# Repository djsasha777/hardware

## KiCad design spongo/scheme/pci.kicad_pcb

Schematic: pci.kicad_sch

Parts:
C1, C2, C3, C4, C5, C6, C7, C8, C9, C10, C11, C12, C13, C14, C15, C16, C17, C18, C19, C20: 0.1uF; D_0603_1608Metric
C2KV1, C2KV2, C2KV3, C2KV4, C2KV5: LD125C274JAB2A; CAPC4532X127N
C200: SIM; D_0603_1608Metric
CSIM1, CSIM2, CSIM3, CSIM4: 33pF; D_0603_1608Metric
IC1, IC2, IC3, IC4, IC5: TMC429-PI24; my-sop-24
J1: Bus_PCI_Express_Mini; BUS_PCI_Express_Mini_Half
J3, J6: Conn_02x09_Odd_Even; PinSocket_2x09_P2.54mm_Vertical
J4: USB4056-03-A_REVA; GCT_USB4056-03-A_REVA; PARTREV A
J5: HDMI_A; HDMI_A_Molex_208658-1001_Horizontal
J7: 1932258-1; CONN_1932258-1
J8: DM3BT-DSF-PEJS; HRS_DM3BT-DSF-PEJS; PARTREV N/A
J9: 78727-0001; 78727-0001_1; Mouser_Part_Number 538-78727-0001
J10: Bus_M.2_Socket_B; TE_1-2199119-0
J11: Conn_02x01_Row_Letter_First; PinSocket_1x02_P2.54mm_Vertical
K1: G6K-2F; RELAY_G6K-2F
PS1: IRM-20-3; Converter_ACDC_MeanWell_IRM-20-xx_THT
PS2: IRM-20-5; Converter_ACDC_MeanWell_IRM-20-xx_THT
R1, R2, R3, R4, R5, R6, R7, R8, R9, R10, R11, R12, R13, R14, R15, R16, R17, R18, R19, R20: 75R; D_0603_1608Metric
RSWITCH1: 330R; D_0603_1608Metric
U1: AC-A; ac-connector
U19: CM4102008; MODULE_CM4102008; PARTREV 2021-10-12
X1, X2, X3: GLX-S-88M
conf5, conf6, conf7, conf8: 330R; D_0603_1608Metric
hlk-1: HLK-7621

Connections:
+3V3: J1.2 (+3V3AUX), J1.52 (+3V3AUX), J6.2, hlk-1.1, hlk-1.2, hlk-1.3, hlk-1.4
+5V: J3.2, J4.A4 (VBUS_A), J4.A9 (VBUS_A), J4.B4 (VBUS_B), J4.B9 (VBUS_B), J5.18 (+5V), J6.8, J7.1 (VBUS), U19.77 (+5V(INPUT)), U19.79 (+5V(INPUT)), U19.81 (+5V(INPUT)), U19.83 (+5V(INPUT)), U19.85 (+5V(INPUT)), U19.87 (+5V(INPUT))
GND: C1.1 (K), C2.1 (K), C2KV1.1, C2KV2.1, C2KV3.1, C2KV4.1, C2KV5.1, C3.1 (K), C4.1 (K), C5.1 (K), C6.1 (K), C7.1 (K), C8.1 (K), C9.1 (K), C10.1 (K), C11.1 (K), C12.1 (K), C13.1 (K), C14.1 (K), C15.1 (K), C16.1 (K), C17.1 (K), C18.1 (K), C19.1 (K), C20.1 (K), C200.1 (K), CSIM1.1 (K), CSIM2.1 (K), CSIM3.1 (K), CSIM4.1 (K), J1.4 (GND), J1.9 (GND), J1.15 (GND), J1.18 (GND), J1.21 (GND), J1.26 (GND), J1.27 (GND), J1.29 (GND), J1.34 (GND), J1.35 (GND), J1.37 (GND), J1.40 (GND), J1.43 (GND), J1.50 (GND), J1.MP, J4.A1 (GND_A), J4.A12 (GND_A), J4.B1 (GND_B), J4.B12 (GND_B), J4.S1 (SHELL_GND), J4.S2 (SHELL_GND), J4.S3 (SHELL_GND), J4.S4 (SHELL_GND), J5.2 (D2S), J5.5 (D1S), J5.8 (D0S), J5.11 (CKS), J5.17 (GND), J5.SH, J6.3, J6.7, J6.11, J6.17, J6.18, J7.4 (GND), J7.7 (GND_DRAIN), J7.S1 (SHIELD), J7.S2 (SHIELD), J8.6 (VSS), J8.S1 (SHIELD), J8.S2 (SHIELD), J8.S3 (SHIELD), J8.S4 (SHIELD), J9.5 (C5), J9.9 (GND1), J9.10 (GND2), J9.11 (GND3), J9.12 (GND4), J9.13 (GND5), J9.14 (GND6), J10.3 (GND), J10.5 (GND), J10.11 (GND), J10.27 (GND), J10.33 (GND), J10.39 (GND), J10.45 (GND), J10.51 (GND), J10.57 (GND), J10.71 (GND), J10.73 (GND), J11.a1, K1.8, PS1.3 (-Vo), PS2.3 (-Vo), RSWITCH1.2 (A), U19.1 (GND), U19.2 (GND), U19.7 (GND), U19.8 (GND), U19.13 (GND), U19.14 (GND), U19.22 (GND), U19.23 (GND), U19.32 (GND), U19.33 (GND), U19.42 (GND), U19.43 (GND), U19.52 (GND), U19.53 (GND), U19.59 (GND), U19.60 (GND), U19.65 (GND), U19.66 (GND), U19.71 (GND), U19.74 (GND), U19.98 (GND), U19.107 (GND), U19.108 (GND), U19.113 (GND), U19.114 (GND), U19.119 (GND), U19.120 (GND), U19.125 (GND), U19.126 (GND), U19.131 (GND), U19.132 (GND), U19.137 (GND), U19.138 (GND), U19.144 (GND), U19.150 (GND), U19.155 (GND), U19.156 (GND), U19.161 (GND), U19.162 (GND), U19.167 (GND), U19.168 (GND), U19.173 (GND), U19.174 (GND), U19.179 (GND), U19.180 (GND), U19.185 (GND), U19.186 (GND), U19.191 (GND), U19.192 (GND), U19.197 (GND), U19.198 (GND), hlk-1.5, hlk-1.6, hlk-1.7, hlk-1.8
unnamed: C1.2 (A), IC1.4 (REF3)
unnamed: C2.2 (A), IC1.10 (SCK_C)
unnamed: C2KV1.2, R1.2 (A), R2.2 (A), R3.2 (A), R4.2 (A)
unnamed: C2KV2.2, R5.2 (A), R6.2 (A), R7.2 (A), R8.2 (A)
unnamed: C2KV3.2, R9.2 (A), R10.2 (A), R11.2 (A), R12.2 (A)
unnamed: C2KV4.2, R13.2 (A), R14.2 (A), R15.2 (A), R16.2 (A)
unnamed: C2KV5.2, R17.2 (A), R18.2 (A), R19.2 (A), R20.2 (A)
unnamed: C3.2 (A), IC1.1 (POSCMP)
unnamed: C4.2 (A), IC1.7 (CLK)
unnamed: C5.2 (A), IC2.4 (REF3)
unnamed: C6.2 (A), IC2.10 (SCK_C)
unnamed: C7.2 (A), IC2.1 (POSCMP)
unnamed: C8.2 (A), IC2.7 (CLK)
unnamed: C9.2 (A), IC3.4 (REF3)
unnamed: C10.2 (A), IC3.10 (SCK_C)
unnamed: C11.2 (A), IC3.1 (POSCMP)
unnamed: C12.2 (A), IC3.7 (CLK)
unnamed: C13.2 (A), IC4.4 (REF3)
unnamed: C14.2 (A), IC4.10 (SCK_C)
unnamed: C15.2 (A), IC4.1 (POSCMP)
unnamed: C16.2 (A), IC4.7 (CLK)
unnamed: C17.2 (A), IC5.4 (REF3)
unnamed: C18.2 (A), IC5.10 (SCK_C)
unnamed: C19.2 (A), IC5.1 (POSCMP)
unnamed: C20.2 (A), IC5.7 (CLK)
unnamed: C200.2 (A), J8.4 (VDD), J10.2 (3.3V), J10.4 (3.3V), J10.70 (3.3V), J10.72 (3.3V), J10.74 (3.3V), U19.75 (SD_PWR_ON), U19.78 (GPIO_VREF), U19.84 (CM4_3.3V(OUTPUT)), U19.86 (CM4_3.3V(OUTPUT)), conf5.2 (A), conf6.2 (A), conf7.2 (A), conf8.2 (A)
unnamed: CSIM1.2 (A), J9.1 (C1), J10.36 (UIM-PWR)
unnamed: CSIM2.2 (A), J9.3 (C3), J10.32 (UIM-CLK)
unnamed: CSIM3.2 (A), J9.7 (C7), J10.34 (UIM-DATA)
unnamed: CSIM4.2 (A), J9.2 (C2), J10.30 (UIM-RESET)
unnamed: IC1.2 (REF1), hlk-1.63
unnamed: IC1.3 (REF2), hlk-1.64
unnamed: IC1.5 (V5@1), hlk-1.65
unnamed: IC1.6 (TEST), hlk-1.66
unnamed: IC1.8 (GND@1), hlk-1.67
unnamed: IC1.9 (~SCS_C), hlk-1.68
unnamed: IC1.11 (SDI_C), hlk-1.69
unnamed: IC1.12 (SDOZ_C), hlk-1.70
unnamed: IC1.13 (REFR2), X1.8
unnamed: IC1.14 (~INT_SDO_C), X1.7
unnamed: IC1.15 (SDO_S_S1), R1.1 (K)
unnamed: IC1.16 (SCK_S_D1), X1.5
unnamed: IC1.17 (~SCS_S_S2), X1.4
unnamed: IC1.18 (~SCS2_S3), R2.1 (K)
unnamed: IC1.19 (~SCS3_D3), X1.6
unnamed: IC1.20 (V5@2), X1.3
unnamed: IC1.21 (V33), R3.1 (K)
unnamed: IC1.22 (GND@2), X1.2
unnamed: IC1.23 (SDI_S_D2), X1.1
unnamed: IC1.24 (REFR1), R4.1 (K)
unnamed: IC2.2 (REF1), hlk-1.36
unnamed: IC2.3 (REF2), hlk-1.37
unnamed: IC2.5 (V5@1), hlk-1.38
unnamed: IC2.6 (TEST), hlk-1.39
unnamed: IC2.8 (GND@1), hlk-1.40
unnamed: IC2.9 (~SCS_C), hlk-1.41
unnamed: IC2.11 (SDI_C), hlk-1.42
unnamed: IC2.12 (SDOZ_C), hlk-1.43
unnamed: IC2.13 (REFR2), X2.8
unnamed: IC2.14 (~INT_SDO_C), X2.7
unnamed: IC2.15 (SDO_S_S1), R6.1 (K)
unnamed: IC2.16 (SCK_S_D1), X2.5
unnamed: IC2.17 (~SCS_S_S2), X2.4
unnamed: IC2.18 (~SCS2_S3), R5.1 (K)
unnamed: IC2.19 (~SCS3_D3), X2.6
unnamed: IC2.20 (V5@2), X2.3
unnamed: IC2.21 (V33), R8.1 (K)
unnamed: IC2.22 (GND@2), X2.2
unnamed: IC2.23 (SDI_S_D2), X2.1
unnamed: IC2.24 (REFR1), R7.1 (K)
unnamed: IC3.2 (REF1), hlk-1.28
unnamed: IC3.3 (REF2), hlk-1.29
unnamed: IC3.5 (V5@1), hlk-1.30
unnamed: IC3.6 (TEST), hlk-1.31
unnamed: IC3.8 (GND@1), hlk-1.32
unnamed: IC3.9 (~SCS_C), hlk-1.33
unnamed: IC3.11 (SDI_C), hlk-1.34
unnamed: IC3.12 (SDOZ_C), hlk-1.35
unnamed: IC3.13 (REFR2), X3.8
unnamed: IC3.14 (~INT_SDO_C), X3.7
unnamed: IC3.15 (SDO_S_S1), R10.1 (K)
unnamed: IC3.16 (SCK_S_D1), X3.5
unnamed: IC3.17 (~SCS_S_S2), X3.4
unnamed: IC3.18 (~SCS2_S3), R9.1 (K)
unnamed: IC3.19 (~SCS3_D3), X3.6
unnamed: IC3.20 (V5@2), X3.3
unnamed: IC3.21 (V33), R12.1 (K)
unnamed: IC3.22 (GND@2), X3.2
unnamed: IC3.23 (SDI_S_D2), X3.1
unnamed: IC3.24 (REFR1), R11.1 (K)
unnamed: IC4.2 (REF1), hlk-1.45
unnamed: IC4.3 (REF2), hlk-1.46
unnamed: IC4.5 (V5@1), hlk-1.47
unnamed: IC4.6 (TEST), hlk-1.48
unnamed: IC4.8 (GND@1), hlk-1.49
unnamed: IC4.9 (~SCS_C), hlk-1.50
unnamed: IC4.11 (SDI_C), hlk-1.51
unnamed: IC4.12 (SDOZ_C), hlk-1.52
unnamed: IC4.13 (REFR2), J3.17
unnamed: IC4.14 (~INT_SDO_C), J3.15
unnamed: IC4.15 (SDO_S_S1), R14.1 (K)
unnamed: IC4.16 (SCK_S_D1), J3.11
unnamed: IC4.17 (~SCS_S_S2), J3.9
unnamed: IC4.18 (~SCS2_S3), R13.1 (K)
unnamed: IC4.19 (~SCS3_D3), J3.13
unnamed: IC4.20 (V5@2), J3.7
unnamed: IC4.21 (V33), R15.1 (K)
unnamed: IC4.22 (GND@2), J3.5
unnamed: IC4.23 (SDI_S_D2), J3.3
unnamed: IC4.24 (REFR1), R16.1 (K)
unnamed: IC5.2 (REF1), U19.12 (ETHERNET_PAIR0_P)
unnamed: IC5.3 (REF2), U19.10 (ETHERNET_PAIR0_N)
unnamed: IC5.5 (V5@1), U19.4 (ETHERNET_PAIR1_P)
unnamed: IC5.6 (TEST), U19.6 (ETHERNET_PAIR1_N)
unnamed: IC5.8 (GND@1), U19.11 (ETHERNET_PAIR2_P)
unnamed: IC5.9 (~SCS_C), U19.9 (ETHERNET_PAIR2_N)
unnamed: IC5.11 (SDI_C), U19.3 (ETHERNET_PAIR3_P)
unnamed: IC5.12 (SDOZ_C), U19.5 (ETHERNET_PAIR3_N)
unnamed: IC5.13 (REFR2), J3.18
unnamed: IC5.14 (~INT_SDO_C), J3.16
unnamed: IC5.15 (SDO_S_S1), R18.1 (K)
unnamed: IC5.16 (SCK_S_D1), J3.12
unnamed: IC5.17 (~SCS_S_S2), J3.10
unnamed: IC5.18 (~SCS2_S3), R17.1 (K)
unnamed: IC5.19 (~SCS3_D3), J3.14
unnamed: IC5.20 (V5@2), J3.8
unnamed: IC5.21 (V33), R19.1 (K)
unnamed: IC5.22 (GND@2), J3.6
unnamed: IC5.23 (SDI_S_D2), J3.4
unnamed: IC5.24 (REFR1), R20.1 (K)
unnamed: J1.11 (REFCLK-), hlk-1.110
unnamed: J1.13 (REFCLK+), hlk-1.111
unnamed: J1.22 (~PERST), hlk-1.105
unnamed: J1.23 (PERn0), hlk-1.109
unnamed: J1.25 (PERp0), hlk-1.108
unnamed: J1.31 (PETn0), hlk-1.107
unnamed: J1.33 (PETp0), hlk-1.106
unnamed: J3.1, PS2.4 (+Vo)
unnamed: J4.A6 (DP1), J4.B6 (DP2), U19.105 (USB_P)
unnamed: J4.A7 (DN1), J4.B7 (DN2), U19.103 (USB_N)
unnamed: J5.1 (D2+), U19.170 (HDMI0_TX2_P)
unnamed: J5.3 (D2-), U19.172 (HDMI0_TX2_N)
unnamed: J5.4 (D1+), U19.176 (HDMI0_TX1_P)
unnamed: J5.6 (D1-), U19.178 (HDMI0_TX1_N)
unnamed: J5.7 (D0+), U19.182 (HDMI0_TX0_P)
unnamed: J5.9 (D0-), U19.184 (HDMI0_TX0_N)
unnamed: J5.10 (CK+), U19.188 (HDMI0_CLK_P)
unnamed: J5.12 (CK-), U19.190 (HDMI0_CLK_N)
unnamed: J5.13 (CEC), U19.151 (HDMI0_CEC)
unnamed: J5.15 (SCL), U19.200 (HDMI0_SCL)
unnamed: J5.16 (SDA), U19.199 (HDMI0_SDA)
unnamed: J5.19 (HPD), U19.153 (HDMI0_HOTPLUG)
unnamed: J6.1, PS1.4 (+Vo)
unnamed: J6.4, U19.93 (~RPIBOOT)
unnamed: J6.5, K1.3, K1.6
unnamed: J6.6, K1.4, K1.5
unnamed: J6.9, U19.28 (GPIO13)
unnamed: J6.10, U19.31 (GPIO12)
unnamed: J6.12, U19.111 (VDAC_COMP)
unnamed: J6.13, hlk-1.94
unnamed: J6.14, U19.55 (GPIO14)
unnamed: J6.15, hlk-1.93
unnamed: J6.16, U19.51 (GPIO15)
unnamed: J7.2 (D-), hlk-1.26
unnamed: J7.3 (D+), hlk-1.25
unnamed: J7.5 (STDA_SSRX-), hlk-1.23
unnamed: J7.6 (STDA_SSRX+), hlk-1.22
unnamed: J7.8 (STDA_SSTX-), hlk-1.21
unnamed: J7.9 (STDA_SSTX+), hlk-1.20
unnamed: J8.1 (DAT2), U19.69 (SD_DAT2)
unnamed: J8.2 (DAT3/CD), U19.61 (SD_DAT3)
unnamed: J8.3 (CMD), U19.62 (SD_CMD)
unnamed: J8.5 (CLK), U19.57 (SD_CLK)
unnamed: J8.7 (DAT0), U19.63 (SD_DAT0)
unnamed: J8.8 (DAT1), U19.67 (SD_DAT1)
unnamed: J10.1 (CONFIG_3), conf8.1 (K)
unnamed: J10.21 (CONFIG_0), conf5.1 (K)
unnamed: J10.41 (PERn0/SATA-B+), U19.118 (PCIE_RX_N)
unnamed: J10.43 (PERp0/SATA-B-), U19.116 (PCIE_RX_P)
unnamed: J10.47 (PETn0/SATA-A-), U19.124 (PCIE_TX_N)
unnamed: J10.49 (PETp0/SATA-A+), U19.122 (PCIE_TX_P)
unnamed: J10.50 (~PERST), U19.109 (PCIE_~RST)
unnamed: J10.52 (~CLKREQ), U19.102 (PCIE_CLK_~REQ)
unnamed: J10.53 (REFCLKn), U19.112 (PCIE_CLK_N)
unnamed: J10.55 (REFCLKp), U19.110 (PCIE_CLK_P)
unnamed: J9.8 (C8), J10.66 (SIM_DETECT)
unnamed: J10.69 (CONFIG_1), conf6.1 (K)
unnamed: J10.75 (CONFIG_2), conf7.1 (K)
unnamed: J11.b1, U19.101 (USB_OTG_ID)
unnamed: K1.1, RSWITCH1.1 (K), hlk-1.104
unnamed: PS1.1 (AC/L), PS2.1 (AC/L), U1.P$1
unnamed: PS1.2 (AC/N), PS2.2 (AC/N), U1.P$2

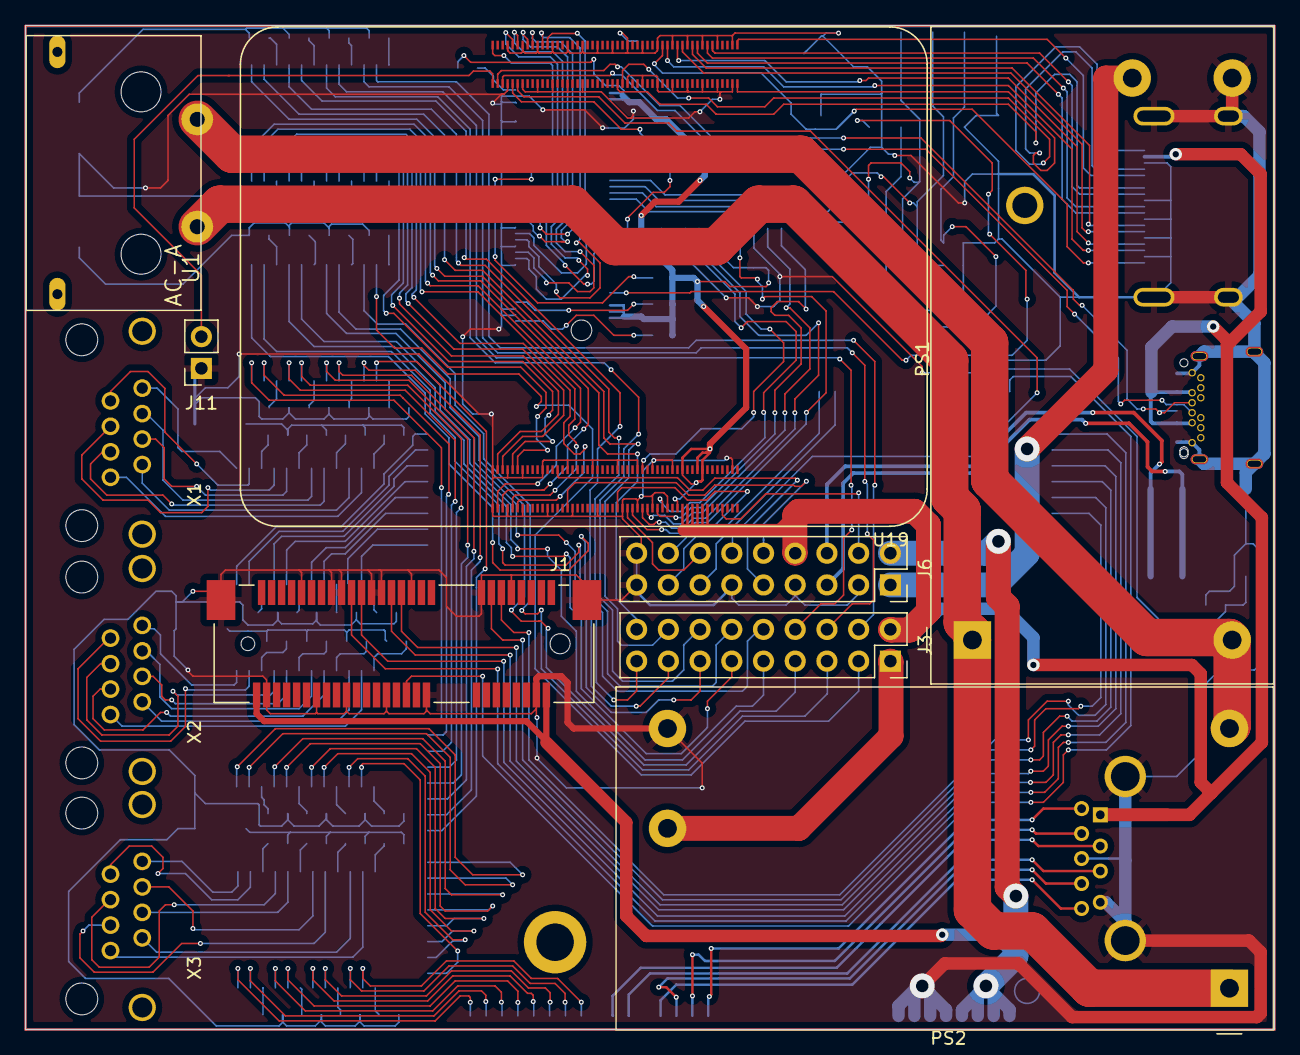
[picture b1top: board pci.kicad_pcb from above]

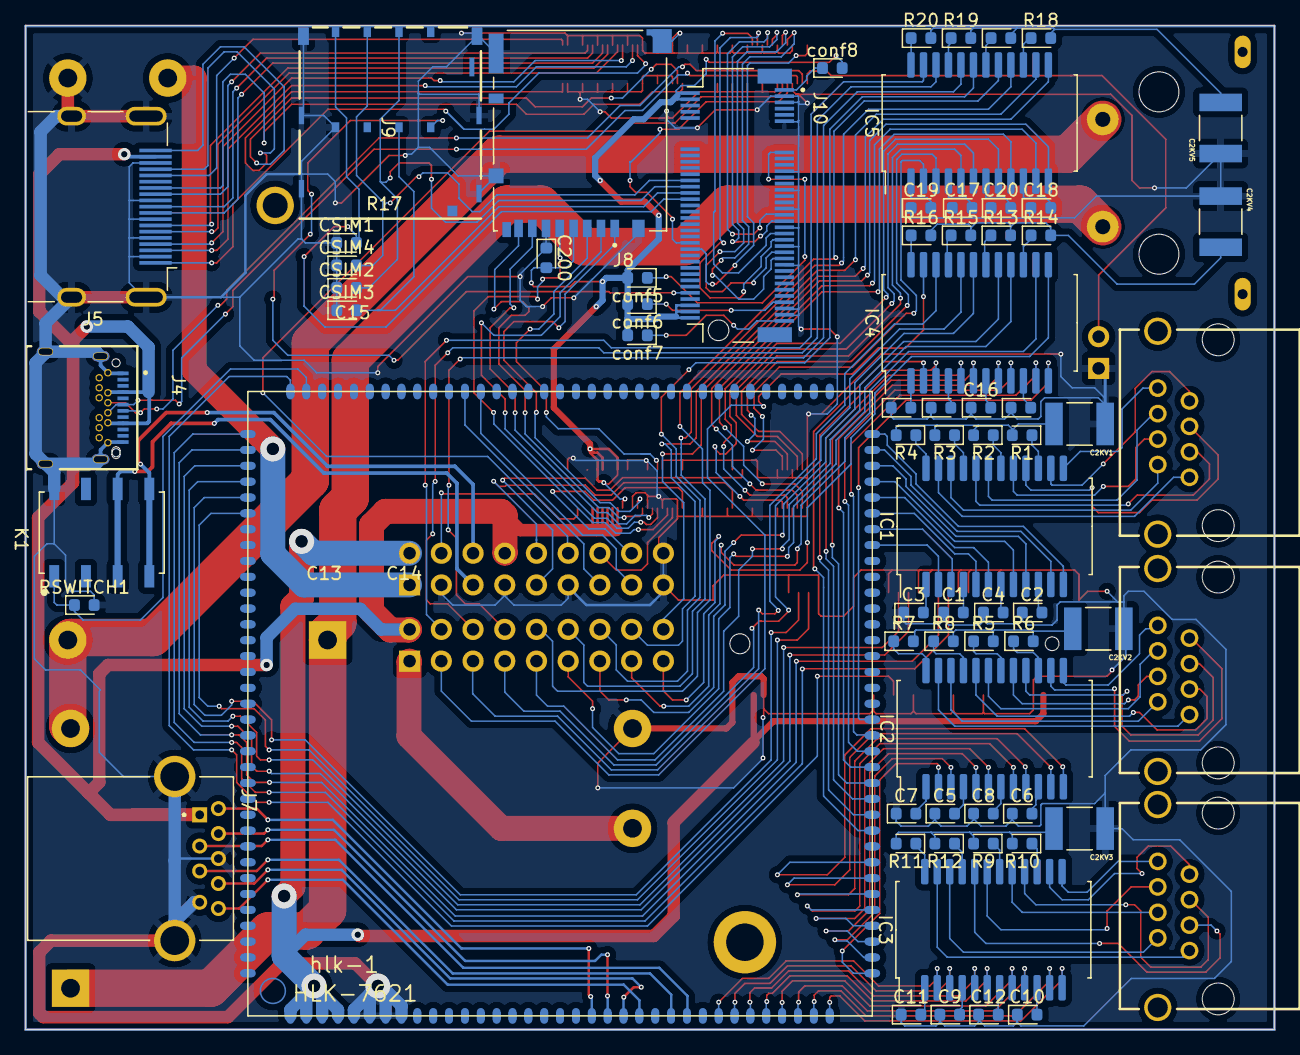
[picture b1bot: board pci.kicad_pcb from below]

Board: 2 copper layers, 100.0 x 80.4 mm, 79 parts (68 on the bottom side), 195 nets.

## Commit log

2025-04-27 nebula
2025-05-03 webdaw
2025-07-14 edit
2025-07-25 uijk
2025-09-11 player 2
2025-09-13 hom4
2025-11-19 test
